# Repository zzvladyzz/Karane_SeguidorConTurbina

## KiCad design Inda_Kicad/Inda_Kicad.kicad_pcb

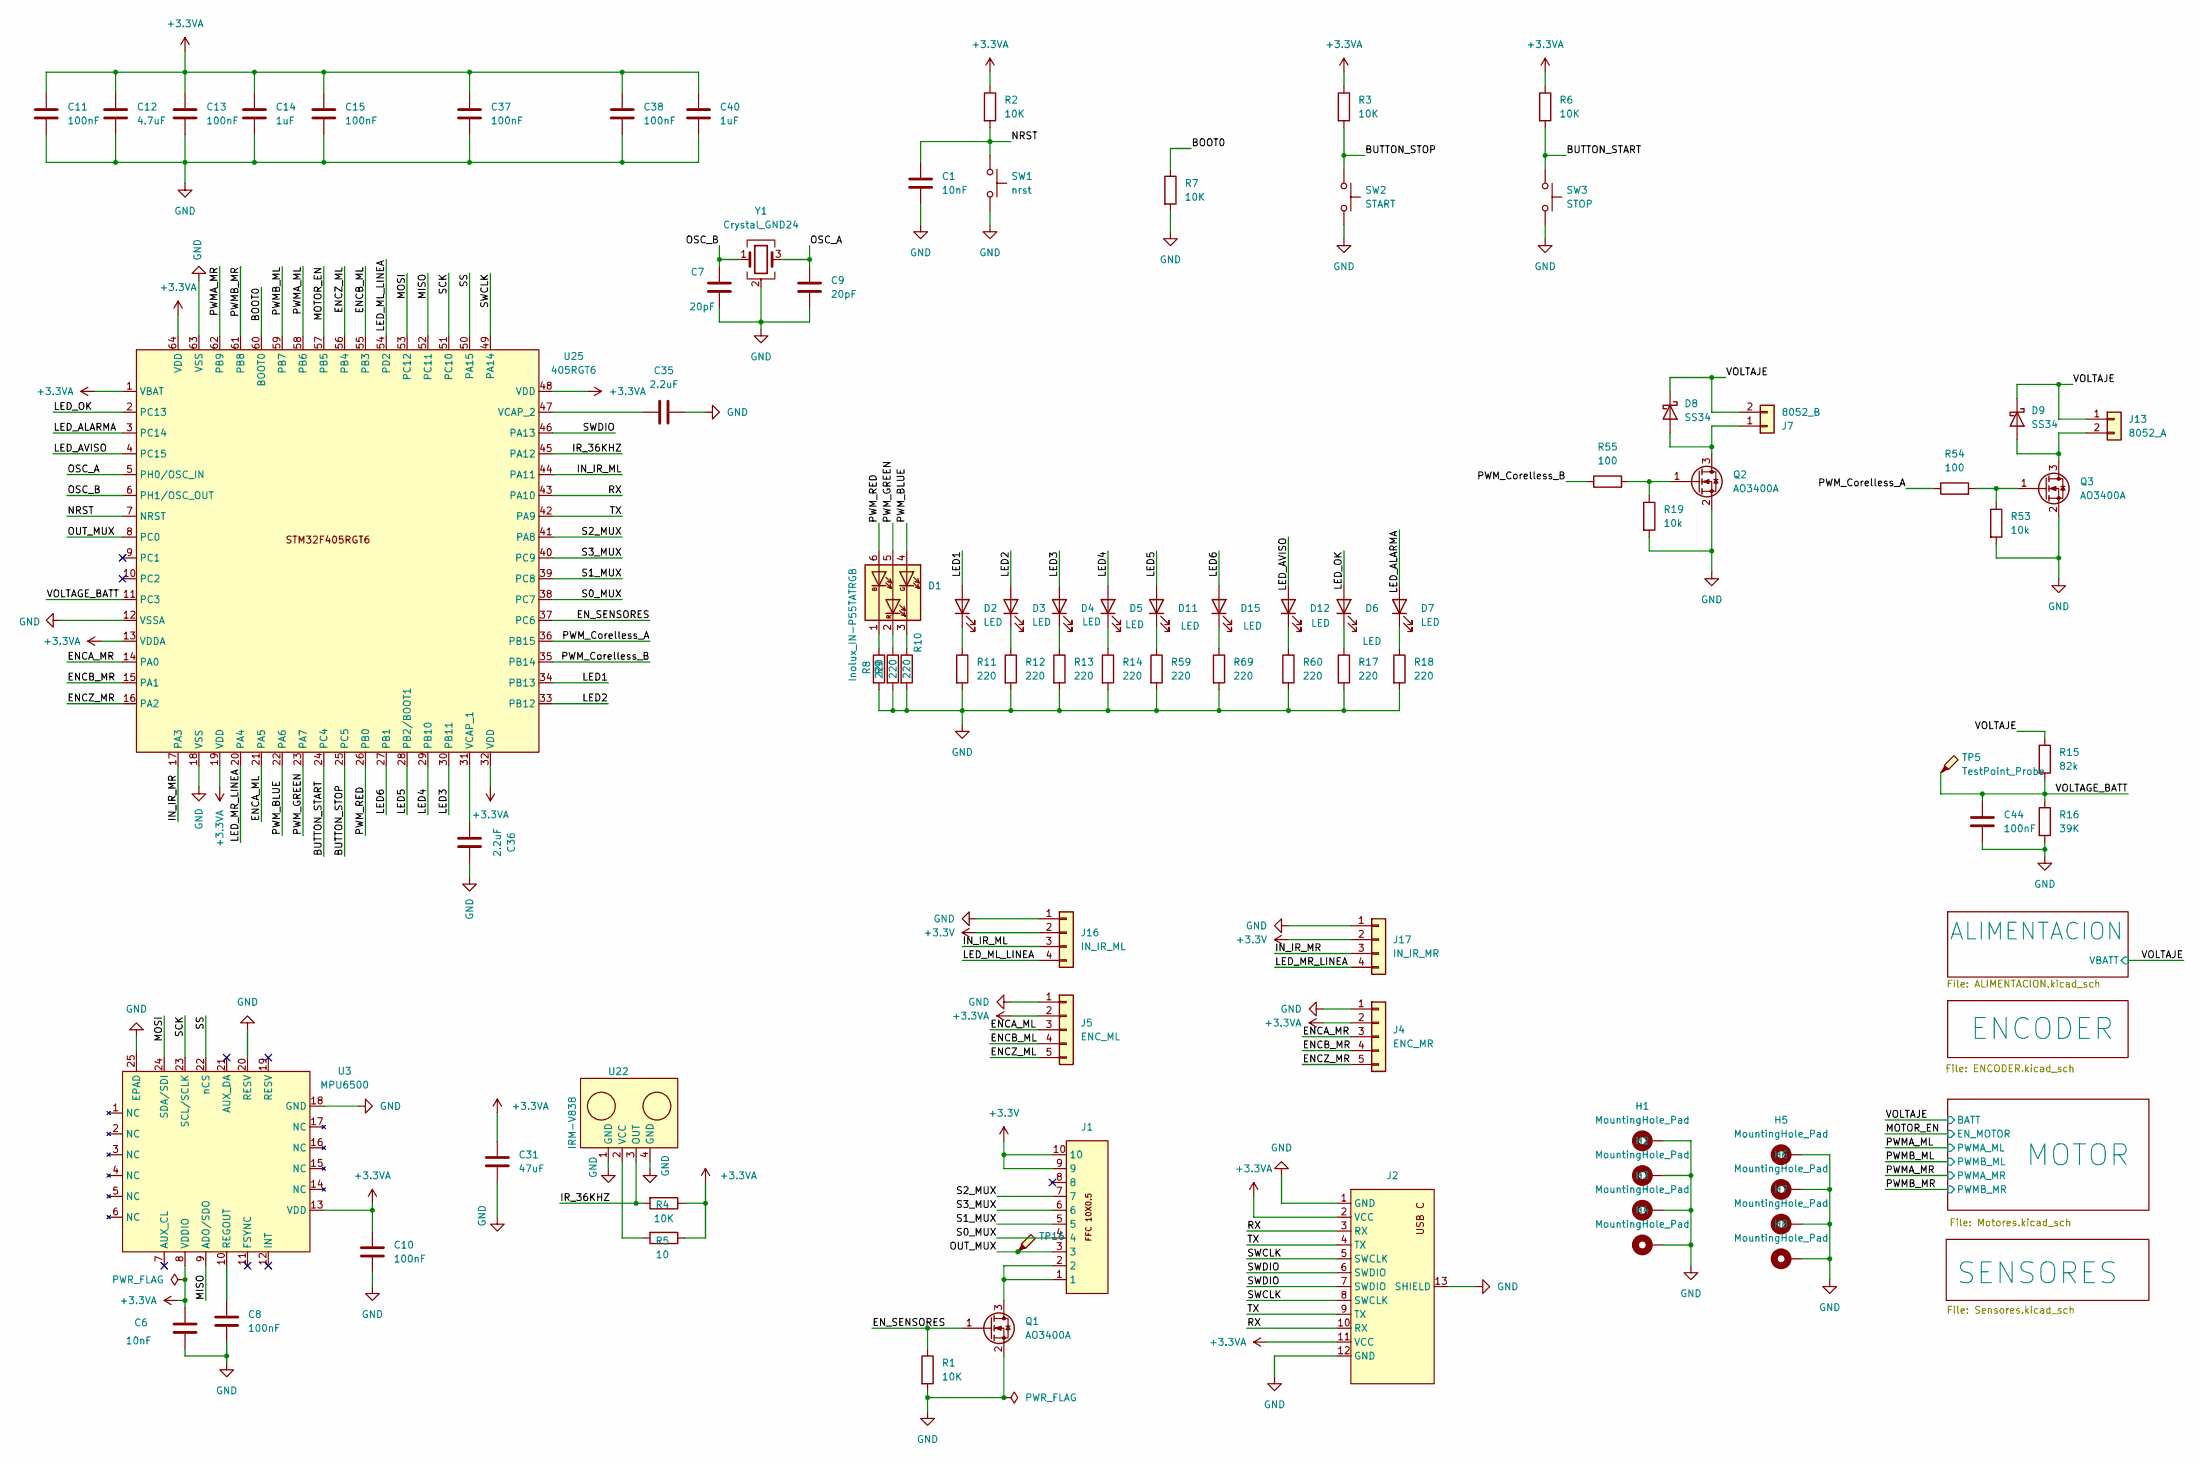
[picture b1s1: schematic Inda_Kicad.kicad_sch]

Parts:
C1, C6: 10nF; C_0603_1608Metric_Pad1.08x0.95mm_HandSolder
C7, C9: 20pF; C_0603_1608Metric_Pad1.08x0.95mm_HandSolder
C8, C10, C11, C13, C15, C37, C38, C44: 100nF; C_0603_1608Metric_Pad1.08x0.95mm_HandSolder
C12: 4.7uF; C_0603_1608Metric_Pad1.08x0.95mm_HandSolder
C14, C40: 1uF; C_0603_1608Metric_Pad1.08x0.95mm_HandSolder
C31: 47uF; C_0603_1608Metric_Pad1.08x0.95mm_HandSolder
C35, C36: 2.2uF; C_0603_1608Metric_Pad1.08x0.95mm_HandSolder
D1: Inolux_IN-P55TATRGB; LED_Inolux_IN-P55TATRGB_PLCC6_5.0x5.5mm_P1.8mm
D2, D3, D4, D5, D6, D7, D11, D12, D15: LED; LED_0805_2012Metric_Pad1.15x1.40mm_HandSolder
D8, D9: SS34; D_SMA
H1, H2, H3, H4, H5, H6, H7, H8: MountingHole_Pad; MountingHole_2.2mm_M2_ISO14580_Pad
J1: FFC_10x0.5
J2: usb_C_stm32
J4: ENC_MR; CONN_MT6701_THT_1.6mm_FEMALE
J5: ENC_ML; CONN_MT6701_THT_1.6mm_FEMALE
J7: 8052_B; JST_PH_B2B-PH-K_1x02_P2.00mm_Vertical
J13: 8052_A; JST_PH_B2B-PH-K_1x02_P2.00mm_Vertical
J16: IN_IR_ML; CONN_01X04_2IR_LINEA_FEMALE
J17: IN_IR_MR; CONN_01X04_2IR_LINEA_FEMALE
Q1, Q2, Q3: AO3400A; SOT-23
R1, R2, R3, R4, R6, R7: 10K; R_0603_1608Metric_Pad0.98x0.95mm_HandSolder
R5: 10; R_0603_1608Metric_Pad0.98x0.95mm_HandSolder
R8, R9, R10, R11, R12, R13, R14, R17, R18, R59, R60, R69: 220; R_0603_1608Metric_Pad0.98x0.95mm_HandSolder
R15: 82k; R_0603_1608Metric_Pad0.98x0.95mm_HandSolder
R16: 39K; R_0603_1608Metric_Pad0.98x0.95mm_HandSolder
R19, R53: 10k; R_0603_1608Metric_Pad0.98x0.95mm_HandSolder
R54, R55: 100; R_0603_1608Metric_Pad0.98x0.95mm_HandSolder
SW1: nrst; SW_Push_SPST_NO_Alps_SKRK
SW2: START; SW_Push_SPST_NO_Alps_SKRK
SW3: STOP; SW_Push_SPST_NO_Alps_SKRK
TP5, TP16: TestPoint_Probe; TestPoint_Pad_D1.0mm
U3: MPU6500; QFN-24-1EP_3x3mm_P0.4mm_EP1.75x1.6mm
U22: IRM-V838
U25: 405RGT6; LQFP-64_10x10mm_P0.5mm
Y1: Crystal_GND24; Crystal_SMD_3225-4Pin_3.2x2.5mm

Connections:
+3.3V: J1.9, J1.10, J16.2, J17.2; also elsewhere on the board
+3.3VA: C6.1, C10.1, C11.1, C12.1, C13.1, C14.1, C15.1, C31.1, C37.1, C38.1, C40.1, J2.2 (VCC), J2.11 (VCC), J4.2, J5.2, R2.1, R3.1, R4.1, R5.1, R6.1, U3.8 (VDDIO), U3.13 (VDD), U25.1 (VBAT), U25.13 (VDDA), U25.19 (VDD), U25.32 (VDD), U25.48 (VDD), U25.64 (VDD); also elsewhere on the board
/BOOT0: R7.1, U25.60 (BOOT0)
/BUTTON_START: R6.2, SW3.1, U25.24 (PC4)
/BUTTON_STOP: R3.2, SW2.1, U25.25 (PC5)
/ENCA_ML: J5.3, U25.21 (PA5)
/ENCA_MR: J4.3, U25.14 (PA0)
/ENCB_ML: J5.4, U25.55 (PB3)
/ENCB_MR: J4.4, U25.15 (PA1)
/ENCZ_ML: J5.5, U25.56 (PB4)
/ENCZ_MR: J4.5, U25.16 (PA2)
/EN_SENSORES: Q1.1 (G), R1.1, U25.37 (PC6)
/IN_IR_ML: J16.3, U25.44 (PA11)
/IN_IR_MR: J17.3, U25.17 (PA3)
/IR_36KHZ: R4.2, U22.3 (OUT), U25.45 (PA12)
/LED1: D2.2 (A), U25.34 (PB13)
/LED2: D3.2 (A), U25.33 (PB12)
/LED3: D4.2 (A), U25.30 (PB11)
/LED4: D5.2 (A), U25.29 (PB10)
/LED5: D11.2 (A), U25.28 (PB2/BOOT1)
/LED6: D15.2 (A), U25.27 (PB1)
/LED_ALARMA: D7.2 (A), U25.3 (PC14)
/LED_AVISO: D12.2 (A), U25.4 (PC15)
/LED_ML_LINEA: J16.4, U25.54 (PD2)
/LED_MR_LINEA: J17.4, U25.20 (PA4)
/LED_OK: D6.2 (A), U25.2 (PC13)
/MISO: U3.9 (ADO/SDO), U25.52 (PC11)
/MOSI: U3.24 (SDA/SDI), U25.53 (PC12)
/MOTOR_EN: U25.57 (PB5); also elsewhere on the board
/NRST: C1.1, R2.2, SW1.1, U25.7 (NRST)
/OSC_A: C9.1, U25.5 (PH0/OSC_IN), Y1.3
/OSC_B: C7.1, U25.6 (PH1/OSC_OUT), Y1.1
/OUT_MUX: J1.3, TP16.1 (1_1), U25.8 (PC0)
/PWMA_ML: U25.58 (PB6); also elsewhere on the board
/PWMA_MR: U25.62 (PB9); also elsewhere on the board
/PWMB_ML: U25.59 (PB7); also elsewhere on the board
/PWMB_MR: U25.61 (PB8); also elsewhere on the board
/PWM_BLUE: D1.4 (AG), U25.22 (PA6)
/PWM_Corelless_A: R54.1, U25.36 (PB15)
/PWM_Corelless_B: R55.1, U25.35 (PB14)
/PWM_GREEN: D1.5 (AR), U25.23 (PA7)
/PWM_RED: D1.6 (AB), U25.26 (PB0)
/RX: J2.3 (RX), J2.10 (RX), U25.43 (PA10)
/S0_MUX: J1.4, U25.38 (PC7)
/S1_MUX: J1.5, U25.39 (PC8)
/S2_MUX: J1.7, U25.41 (PA8)
/S3_MUX: J1.6, U25.40 (PC9)
/SCK: U3.23 (SCL/SCLK), U25.51 (PC10)
/SS: U3.22 (nCS), U25.50 (PA15)
/SWCLK: J2.5 (SWCLK), J2.8 (SWCLK), U25.49 (PA14)
/SWDIO: J2.6 (SWDIO), J2.7 (SWDIO), U25.46 (PA13)
/TX: J2.4 (TX), J2.9 (TX), U25.42 (PA9)
/VOLTAGE_BATT: C44.1, R15.2, R16.1, TP5.1 (1_1), U25.11 (PC3)
/VOLTAJE: D8.1 (K), D9.1 (K), J7.2, J13.1, R15.1; also elsewhere on the board
GND: C1.2, C6.2, C7.2, C8.2, C9.2, C10.2, C11.2, C12.2, C13.2, C14.2, C15.2, C31.2, C35.2, C36.2, C37.2, C38.2, C40.2, C44.2, H1.1 (1_1), H2.1 (1_1), H3.1 (1_1), H4.1 (1_1), H5.1 (1_1), H6.1 (1_1), H7.1 (1_1), H8.1 (1_1), J2.1 (GND), J2.12 (GND), J2.13 (SHIELD), J4.1, J5.1, J16.1, J17.1, Q1.2 (S), Q2.2 (S), Q3.2 (S), R1.2, R7.2, R8.2, R9.2, R10.2, R11.2, R12.2, R13.2, R14.2, R16.2, R17.2, R18.2, R19.2, R53.2, R59.2, R60.2, R69.2, SW1.2, SW2.2, SW3.2, U3.18 (GND), U3.20 (RESV), U3.25 (EPAD), U22.1 (GND), U22.4 (GND), U25.12 (VSSA), U25.18 (VSS), U25.63 (VSS), Y1.2 (G), Y1.4 (G); also elsewhere on the board
unnamed: D1.1 (KB), R8.1
unnamed: D1.3 (KG), R10.1
unnamed: D1.2 (KR), R9.1
unnamed: D2.1 (K), R11.1
unnamed: D3.1 (K), R12.1
unnamed: D4.1 (K), R13.1
unnamed: D5.1 (K), R14.1
unnamed: D6.1 (K), R17.1
unnamed: D7.1 (K), R18.1
unnamed: D8.2 (A), J7.1, Q2.3 (D)
unnamed: D9.2 (A), J13.2, Q3.3 (D)
unnamed: D11.1 (K), R59.1
unnamed: D12.1 (K), R60.1
unnamed: D15.1 (K), R69.1
unnamed: J1.1, J1.2, Q1.3 (D)
unnamed: Q2.1 (G), R19.1, R55.2
unnamed: Q3.1 (G), R53.1, R54.2
unnamed: C8.1, U3.10 (REGOUT)
unnamed: R5.2, U22.2 (VCC)
unnamed: C36.1, U25.31 (VCAP_1)
unnamed: C35.1, U25.47 (VCAP_2)

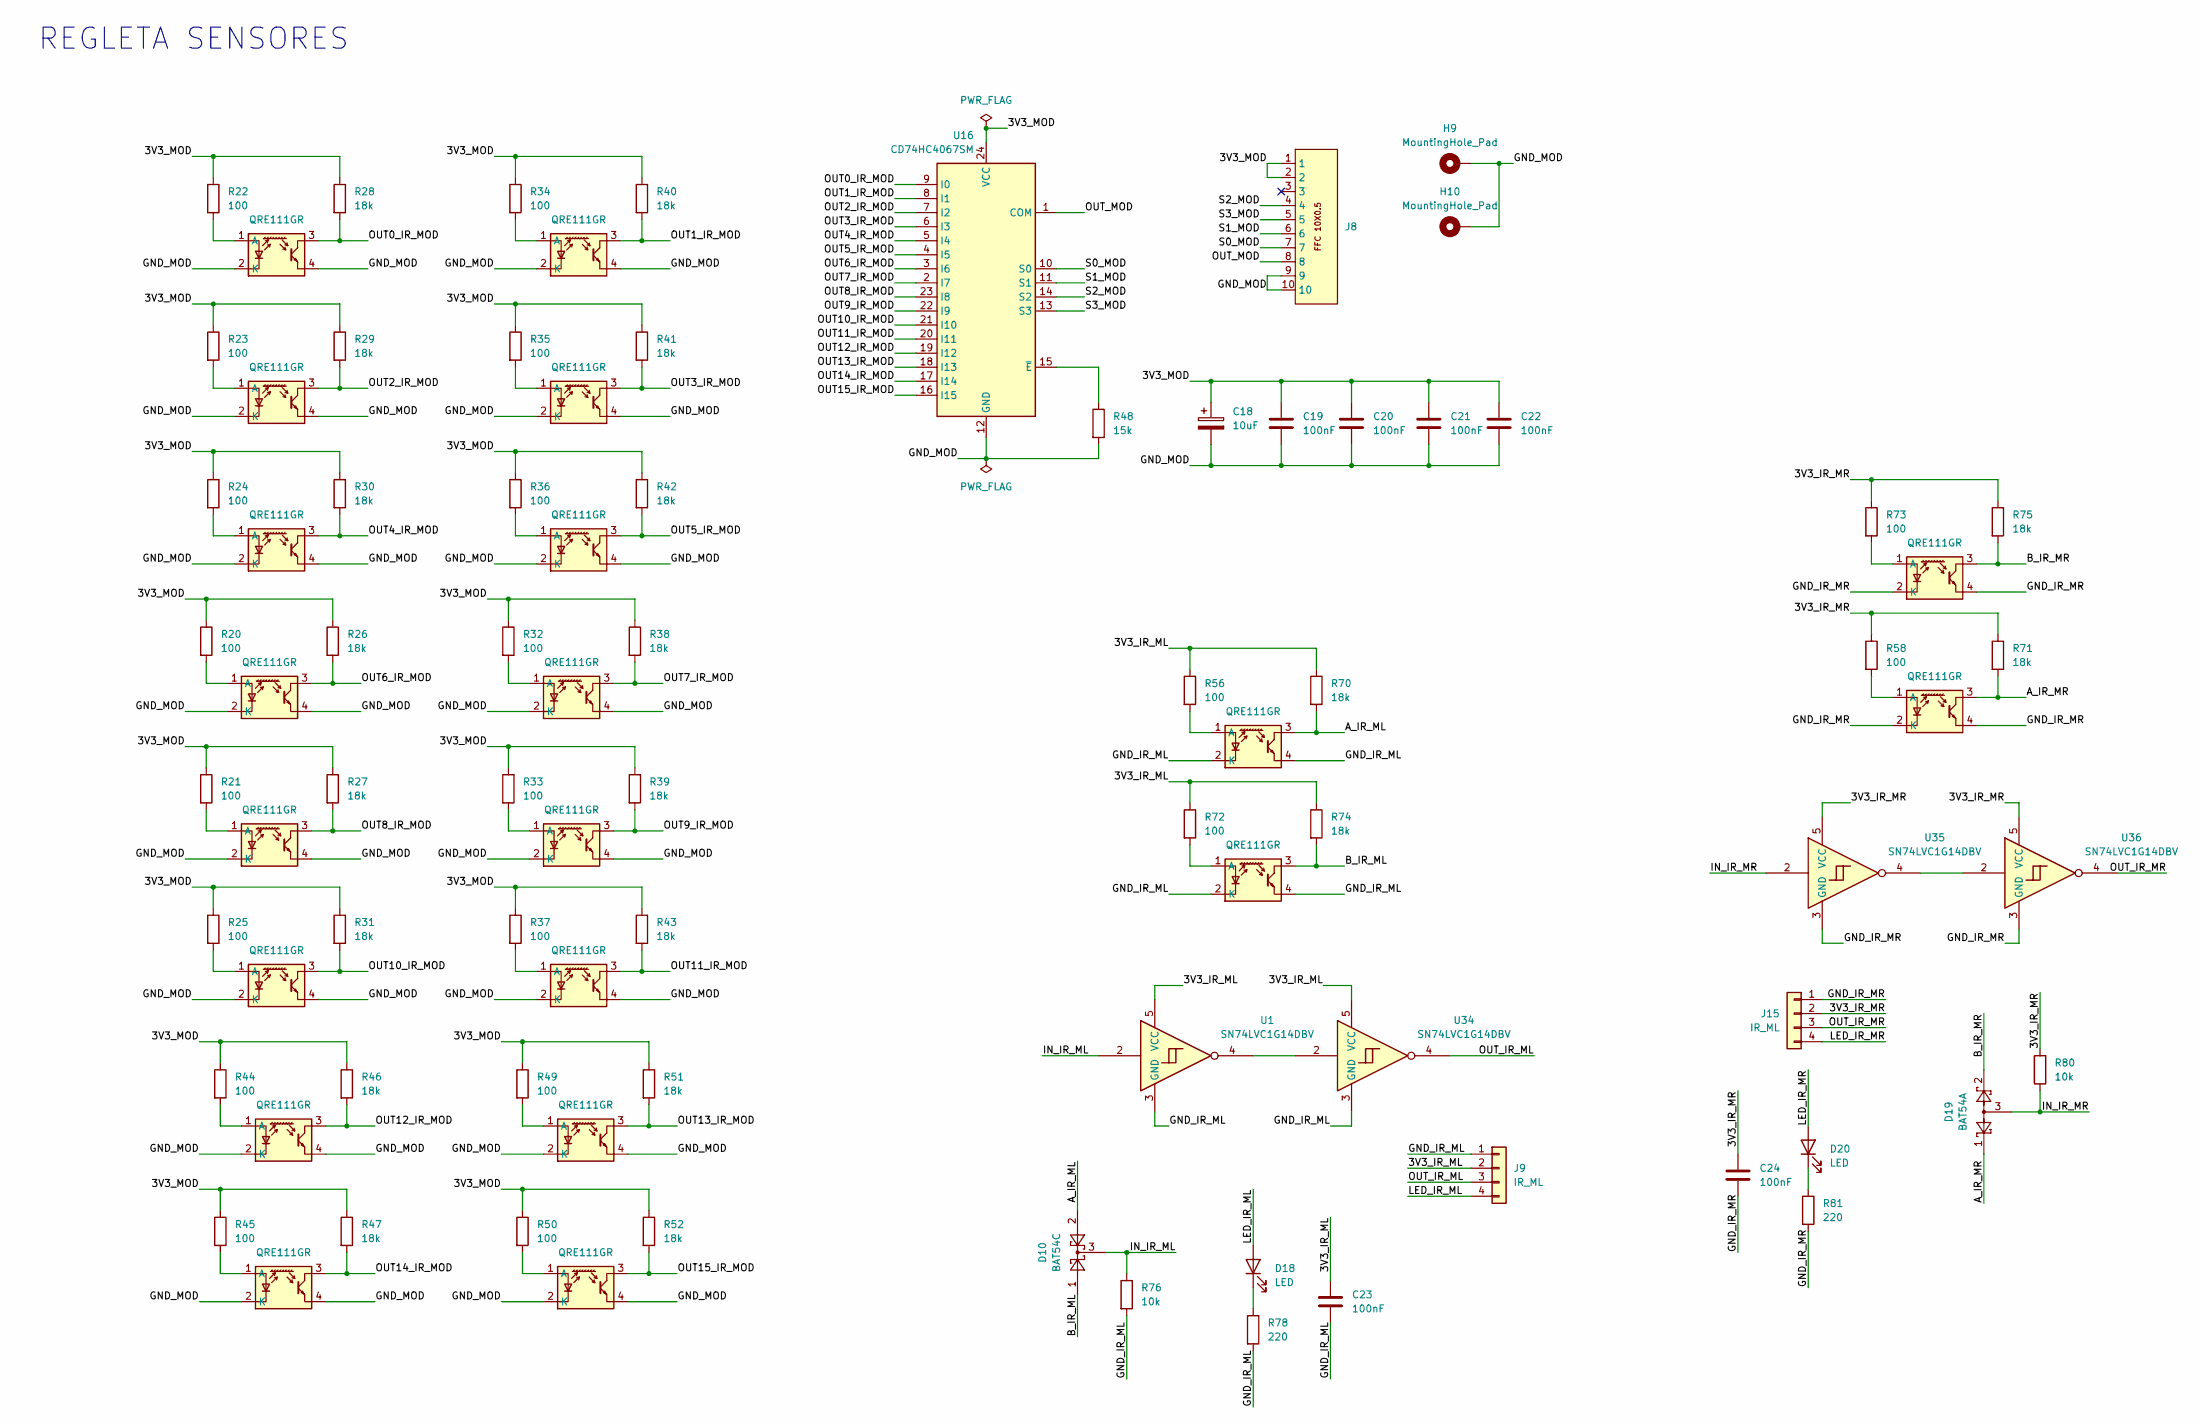
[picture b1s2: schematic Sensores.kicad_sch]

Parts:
C18: 10uF; CP_EIA-3216-12_Kemet-S
C19, C20, C21, C22, C23, C24: 100nF; C_0603_1608Metric_Pad1.08x0.95mm_HandSolder
D10: BAT54C; SOT-23
D18, D20: LED; LED_1206_3216Metric_Pad1.42x1.75mm_HandSolder
D19: BAT54A; SOT-23
H9, H10: MountingHole_Pad; MountingHole_2.2mm_M2_ISO14580_Pad
J8: FFC_10x0.5
J9, J15: IR_ML; CONN_01X04_2IR_LINEA_MALE
R20, R21, R22, R23, R24, R25, R32, R33, R34, R35, R36, R37, R44, R45, R49, R50, R56, R58, R72, R73: 100; R_0603_1608Metric_Pad0.98x0.95mm_HandSolder
R26, R27, R28, R29, R30, R31, R38, R39, R40, R41, R42, R43, R46, R47, R51, R52, R70, R71, R74, R75: 18k; R_0603_1608Metric_Pad0.98x0.95mm_HandSolder
R48: 15k; R_0603_1608Metric_Pad0.98x0.95mm_HandSolder
R76, R80: 10k; R_0603_1608Metric_Pad0.98x0.95mm_HandSolder
R78, R81: 220; R_0603_1608Metric_Pad0.98x0.95mm_HandSolder
U1, U34, U35, U36: SN74LVC1G14DBV; SOT-23-5
U4, U5, U6, U7, U8, U9, U10, U11, U12, U13, U14, U15, U17, U18, U19, U20, U30, U31, U32, U33: QRE111GR; QRE1113GR_IR
U16: CD74HC4067SM; SSOP-24_5.3x8.2mm_P0.65mm

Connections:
/SENSORES/3V3_IR_ML: C23.1, J9.2, R56.1, R70.1, R72.1, R74.1, U1.5 (VCC), U34.5 (VCC)
/SENSORES/3V3_IR_MR: C24.1, J15.2, R58.1, R71.1, R73.1, R75.1, R80.2, U35.5 (VCC), U36.5 (VCC)
/SENSORES/3V3_MOD: C18.1, C19.1, C20.1, C21.1, C22.1, J8.1, J8.2, R20.1, R21.1, R22.1, R23.1, R24.1, R25.1, R26.1, R27.1, R28.1, R29.1, R30.1, R31.1, R32.1, R33.1, R34.1, R35.1, R36.1, R37.1, R38.1, R39.1, R40.1, R41.1, R42.1, R43.1, R44.1, R45.1, R46.1, R47.1, R49.1, R50.1, R51.1, R52.1, U16.24 (VCC)
/SENSORES/A_IR_ML: D10.2, R70.2, U30.3
/SENSORES/A_IR_MR: D19.1, R71.2, U31.3
/SENSORES/B_IR_ML: D10.1, R74.2, U32.3
/SENSORES/B_IR_MR: D19.2, R75.2, U33.3
/SENSORES/GND_IR_ML: C23.2, J9.1, R76.2, R78.2, U1.3 (GND), U30.2 (K), U30.4, U32.2 (K), U32.4, U34.3 (GND)
/SENSORES/GND_IR_MR: C24.2, J15.1, R81.2, U31.2 (K), U31.4, U33.2 (K), U33.4, U35.3 (GND), U36.3 (GND)
/SENSORES/GND_MOD: C18.2, C19.2, C20.2, C21.2, C22.2, H9.1 (1_1), H10.1 (1_1), J8.9, J8.10, R48.2, U4.2 (K), U4.4, U5.2 (K), U5.4, U6.2 (K), U6.4, U7.2 (K), U7.4, U8.2 (K), U8.4, U9.2 (K), U9.4, U10.2 (K), U10.4, U11.2 (K), U11.4, U12.2 (K), U12.4, U13.2 (K), U13.4, U14.2 (K), U14.4, U15.2 (K), U15.4, U16.12 (GND), U17.2 (K), U17.4, U18.2 (K), U18.4, U19.2 (K), U19.4, U20.2 (K), U20.4
/SENSORES/IN_IR_ML: D10.3, R76.1, U1.2
/SENSORES/IN_IR_MR: D19.3, R80.1, U35.2
/SENSORES/LED_IR_ML: D18.2 (A), J9.4
/SENSORES/LED_IR_MR: D20.2 (A), J15.4
/SENSORES/OUT0_IR_MOD: R28.2, U6.3, U16.9 (I0)
/SENSORES/OUT1_IR_MOD: R40.2, U12.3, U16.8 (I1)
/SENSORES/OUT2_IR_MOD: R29.2, U7.3, U16.7 (I2)
/SENSORES/OUT3_IR_MOD: R41.2, U13.3, U16.6 (I3)
/SENSORES/OUT4_IR_MOD: R30.2, U8.3, U16.5 (I4)
/SENSORES/OUT5_IR_MOD: R42.2, U14.3, U16.4 (I5)
/SENSORES/OUT6_IR_MOD: R26.2, U4.3, U16.3 (I6)
/SENSORES/OUT7_IR_MOD: R38.2, U10.3, U16.2 (I7)
/SENSORES/OUT8_IR_MOD: R27.2, U5.3, U16.23 (I8)
/SENSORES/OUT9_IR_MOD: R39.2, U11.3, U16.22 (I9)
/SENSORES/OUT10_IR_MOD: R31.2, U9.3, U16.21 (I10)
/SENSORES/OUT11_IR_MOD: R43.2, U15.3, U16.20 (I11)
/SENSORES/OUT12_IR_MOD: R46.2, U16.19 (I12), U17.3
/SENSORES/OUT13_IR_MOD: R51.2, U16.18 (I13), U19.3
/SENSORES/OUT14_IR_MOD: R47.2, U16.17 (I14), U18.3
/SENSORES/OUT15_IR_MOD: R52.2, U16.16 (I15), U20.3
/SENSORES/OUT_IR_ML: J9.3, U34.4
/SENSORES/OUT_IR_MR: J15.3, U36.4
/SENSORES/OUT_MOD: J8.8, U16.1 (COM)
/SENSORES/S0_MOD: J8.7, U16.10 (S0)
/SENSORES/S1_MOD: J8.6, U16.11 (S1)
/SENSORES/S2_MOD: J8.4, U16.14 (S2)
/SENSORES/S3_MOD: J8.5, U16.13 (S3)
unnamed: D18.1 (K), R78.1
unnamed: D20.1 (K), R81.1
unnamed: U1.4, U34.2
unnamed: R20.2, U4.1 (A)
unnamed: R21.2, U5.1 (A)
unnamed: R22.2, U6.1 (A)
unnamed: R23.2, U7.1 (A)
unnamed: R24.2, U8.1 (A)
unnamed: R25.2, U9.1 (A)
unnamed: R32.2, U10.1 (A)
unnamed: R33.2, U11.1 (A)
unnamed: R34.2, U12.1 (A)
unnamed: R35.2, U13.1 (A)
unnamed: R36.2, U14.1 (A)
unnamed: R37.2, U15.1 (A)
unnamed: R48.1, U16.15 (~E)
unnamed: R44.2, U17.1 (A)
unnamed: R45.2, U18.1 (A)
unnamed: R49.2, U19.1 (A)
unnamed: R50.2, U20.1 (A)
unnamed: R56.2, U30.1 (A)
unnamed: R58.2, U31.1 (A)
unnamed: R72.2, U32.1 (A)
unnamed: R73.2, U33.1 (A)
unnamed: U35.4, U36.2

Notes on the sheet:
REGLETA SENSORES

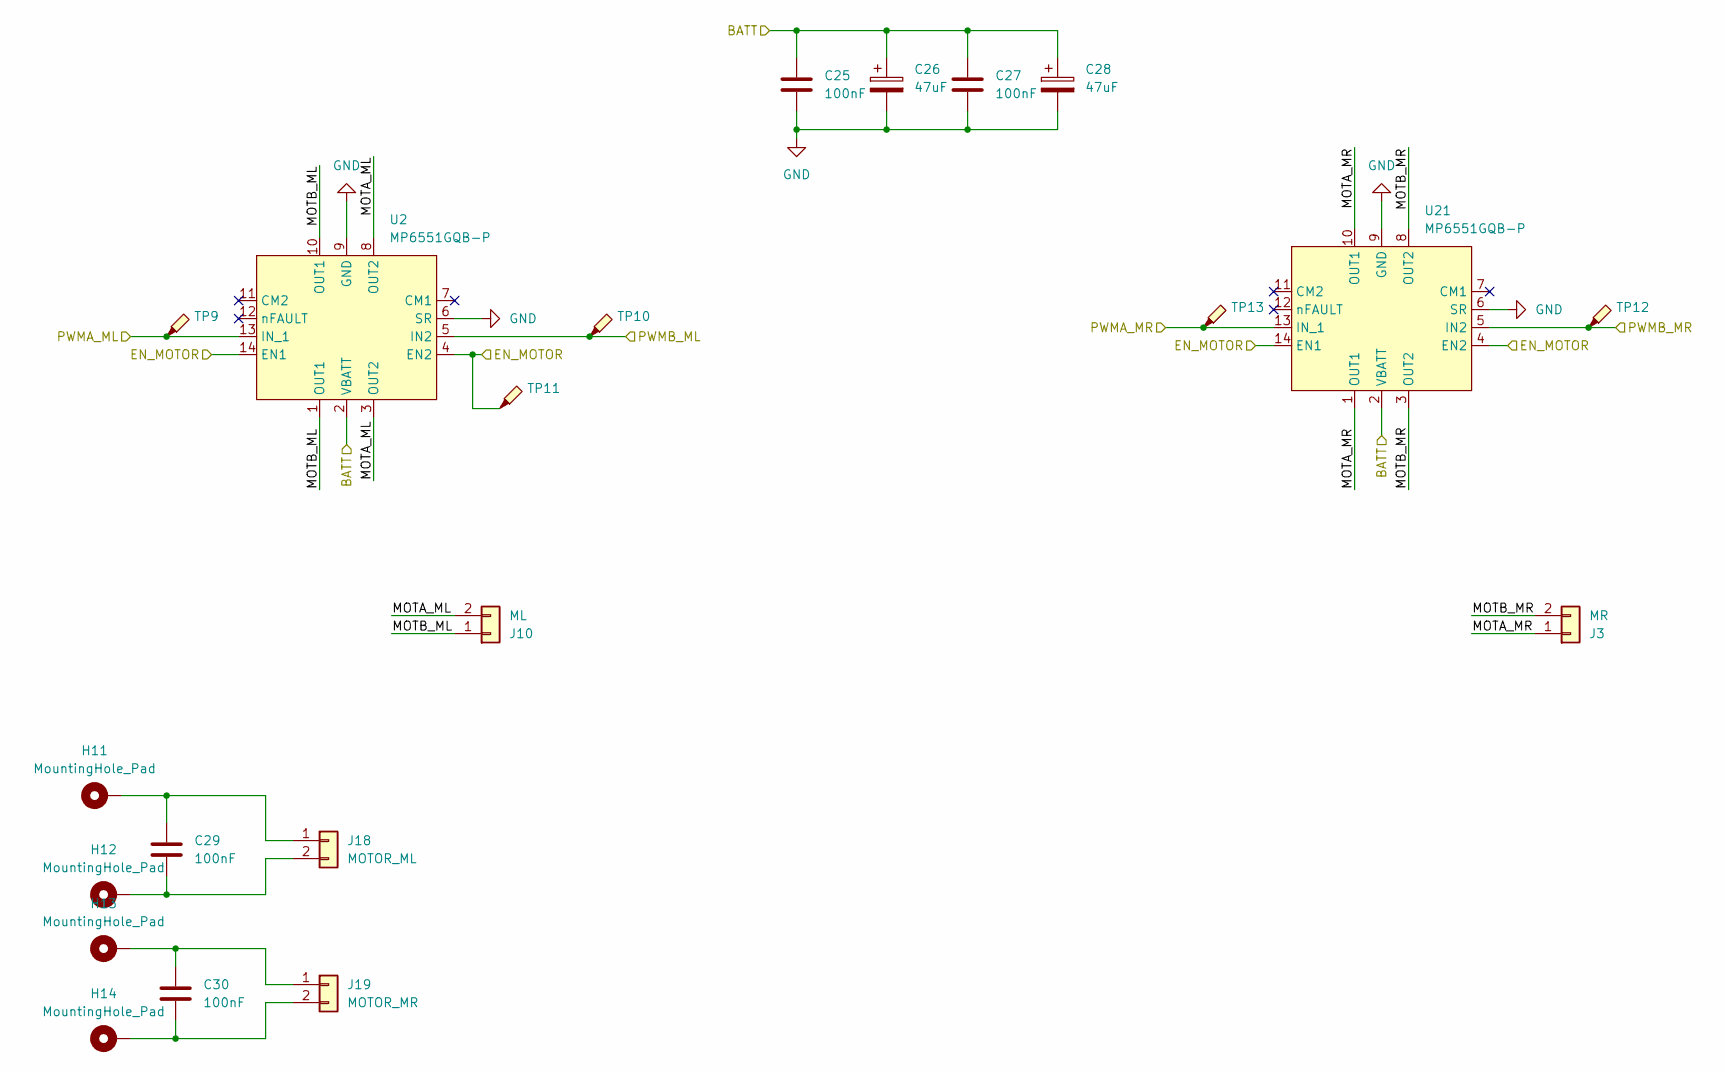
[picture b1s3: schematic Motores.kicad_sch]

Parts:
C25, C27: 100nF; C_0603_1608Metric_Pad1.08x0.95mm_HandSolder
C26, C28: 47uF; CP_EIA-7343-15_Kemet-W_HandSolder
C29, C30: 100nF; C_0805_2012Metric_Pad1.18x1.45mm_HandSolder
H11, H12, H13, H14: MountingHole_Pad; PAD_MOTOR_1725
J3: MR; JST_PH_B2B-PH-K_1x02_P2.00mm_Vertical
J10: ML; JST_PH_B2B-PH-K_1x02_P2.00mm_Vertical
J18: MOTOR_ML; JST_PH_S2B-PH-K_1x02_P2.00mm_Horizontal
J19: MOTOR_MR; JST_PH_S2B-PH-K_1x02_P2.00mm_Horizontal
TP9, TP10, TP11, TP12, TP13: TestPoint_Probe; TestPoint_Pad_D1.0mm
U2, U21: MP6551GQB-P; MP6551

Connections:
/MOTOR/MOTA_ML: J10.2, U2.3 (OUT2), U2.8 (OUT2)
/MOTOR/MOTA_MR: J3.1, U21.1 (OUT1), U21.10 (OUT1)
/MOTOR/MOTB_ML: J10.1, U2.1 (OUT1), U2.10 (OUT1)
/MOTOR/MOTB_MR: J3.2, U21.3 (OUT2), U21.8 (OUT2)
/MOTOR_EN: TP11.1 (1_1), U2.4 (EN2), U2.14 (EN1), U21.4 (EN2), U21.14 (EN1); also elsewhere on the board
/PWMA_ML: TP9.1 (1_1), U2.13 (IN_1); also elsewhere on the board
/PWMA_MR: TP13.1 (1_1), U21.13 (IN_1); also elsewhere on the board
/PWMB_ML: TP10.1 (1_1), U2.5 (IN2); also elsewhere on the board
/PWMB_MR: TP12.1 (1_1), U21.5 (IN2); also elsewhere on the board
/VOLTAJE: C25.1, C26.1, C27.1, C28.1, U2.2 (VBATT), U21.2 (VBATT); also elsewhere on the board
GND: C25.2, C26.2, C27.2, C28.2, U2.6 (SR), U2.9 (GND), U21.6 (SR), U21.9 (GND); also elsewhere on the board
unnamed: C29.1, H11.1 (1_1), J18.1
unnamed: C29.2, H12.1 (1_1), J18.2
unnamed: C30.1, H13.1 (1_1), J19.1
unnamed: C30.2, H14.1 (1_1), J19.2

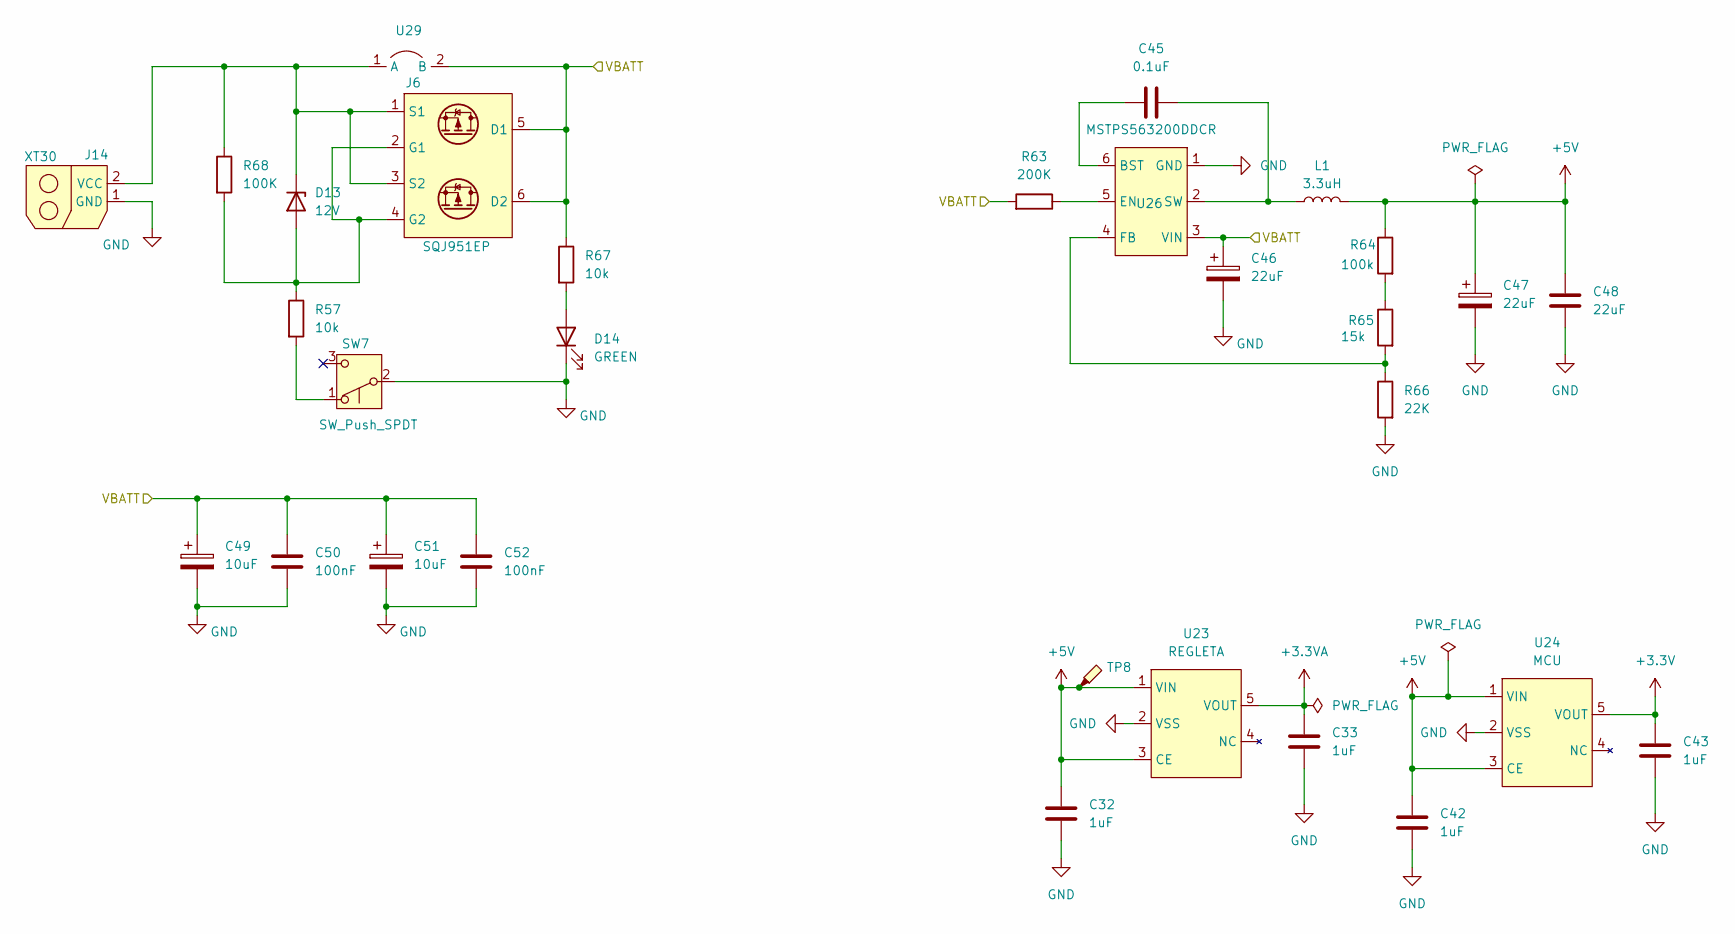
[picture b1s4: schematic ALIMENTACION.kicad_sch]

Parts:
C32, C33, C42, C43: 1uF; C_0603_1608Metric_Pad1.08x0.95mm_HandSolder
C45: 0.1uF; C_0603_1608Metric
C46, C47: 22uF; CP_EIA-3528-15_AVX-H_HandSolder
C48: 22uF; C_0603_1608Metric
C49, C51: 10uF; CP_EIA-3528-15_AVX-H_HandSolder
C50, C52: 100nF; C_0603_1608Metric
D13: 12V; R_1206_3216Metric_Pad1.30x1.75mm_HandSolder
D14: GREEN; LED_1206_3216Metric_Pad1.42x1.75mm_HandSolder
J6: SQJ951EP; PowerPAK_SO-8_Dual
J14: XT30; XT30U-F_1x02_P5.0mm_Vertical
L1: 3.3uH; L_Sunlord_MWSA0402S
R57, R67: 10k; R_0603_1608Metric_Pad0.98x0.95mm_HandSolder
R63: 200K; R_0603_1608Metric_Pad0.98x0.95mm_HandSolder
R64: 100k; R_0603_1608Metric_Pad0.98x0.95mm_HandSolder
R65: 15k; R_0603_1608Metric_Pad0.98x0.95mm_HandSolder
R66: 22K; R_0603_1608Metric_Pad0.98x0.95mm_HandSolder
R68: 100K; R_0603_1608Metric_Pad0.98x0.95mm_HandSolder
SW7: SW_Push_SPDT; SW_SPDT_PCM12
TP8: TestPoint_Probe; TestPoint_Pad_D1.0mm
U23: REGLETA; SOT-23-5_HandSoldering
U24: MCU; SOT-23-5_HandSoldering
U26: MSTPS563200DDCR; SOT-23-6
U29: BRIDGE_2P

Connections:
+3.3V: C43.1, U24.5 (VOUT); also elsewhere on the board
+3.3VA: C33.1, U23.5 (VOUT); also elsewhere on the board
+5V: C32.1, C42.1, C47.1, C48.2, L1.1, R64.1, TP8.1 (1_1), U23.1 (VIN), U23.3 (CE), U24.1 (VIN), U24.3 (CE)
/VOLTAJE: C46.1, C49.1, C50.2, C51.1, C52.2, J6.5 (D1), J6.6 (D2), R63.2, R67.1, U26.3 (VIN), U29.2 (B); also elsewhere on the board
GND: C32.2, C33.2, C42.2, C43.2, C46.2, C47.2, C48.1, C49.2, C50.1, C51.2, C52.1, D14.1 (K), J14.1 (GND), R66.2, SW7.2 (B), U23.2 (VSS), U24.2 (VSS), U26.1 (GND); also elsewhere on the board
unnamed: D13.2 (A), J6.2 (G1), J6.4 (G2), R57.1, R68.2
unnamed: D13.1 (K), J6.1 (S1), J6.3 (S2), J14.2 (VCC), R68.1, U29.1 (A)
unnamed: D14.2 (A), R67.2
unnamed: R64.2, R65.1
unnamed: R57.2, SW7.1 (A)
unnamed: C45.1, U26.6 (BST)
unnamed: R63.1, U26.5 (EN)
unnamed: R65.2, R66.1, U26.4 (FB)
unnamed: C45.2, L1.2, U26.2 (SW)

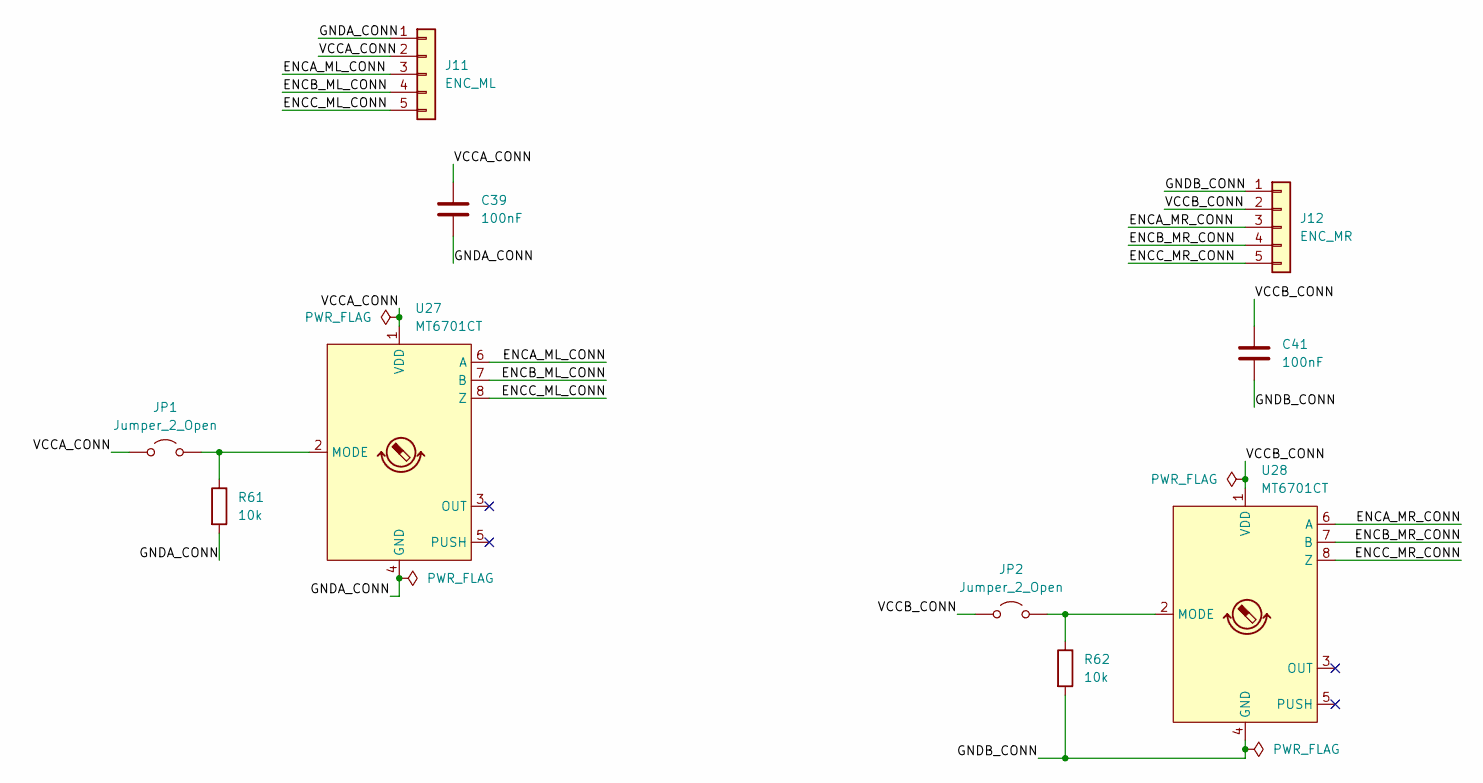
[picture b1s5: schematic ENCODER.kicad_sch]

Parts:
C39, C41: 100nF; C_0603_1608Metric_Pad1.08x0.95mm_HandSolder
J11: ENC_ML; CONN_MT6701_THT_1.6mm_MALE
J12: ENC_MR; CONN_MT6701_THT_1.6mm_MALE
JP1, JP2: Jumper_2_Open; SolderJumper-2_P1.3mm_Open_RoundedPad1.0x1.5mm
R61, R62: 10k; R_0603_1608Metric_Pad0.98x0.95mm_HandSolder
U27, U28: MT6701CT; SO-8_3.9x4.9mm_P1.27mm

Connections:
/ENCODER/ENCA_ML_CONN: J11.3, U27.6 (A)
/ENCODER/ENCA_MR_CONN: J12.3, U28.6 (A)
/ENCODER/ENCB_ML_CONN: J11.4, U27.7 (B)
/ENCODER/ENCB_MR_CONN: J12.4, U28.7 (B)
/ENCODER/ENCC_ML_CONN: J11.5, U27.8 (Z)
/ENCODER/ENCC_MR_CONN: J12.5, U28.8 (Z)
/ENCODER/GNDA_CONN: C39.2, J11.1, R61.2, U27.4 (GND)
/ENCODER/GNDB_CONN: C41.2, J12.1, R62.2, U28.4 (GND)
/ENCODER/VCCA_CONN: C39.1, J11.2, JP1.1 (A), U27.1 (VDD)
/ENCODER/VCCB_CONN: C41.1, J12.2, JP2.1 (A), U28.1 (VDD)
unnamed: JP1.2 (B), R61.1, U27.2 (MODE)
unnamed: JP2.2 (B), R62.1, U28.2 (MODE)

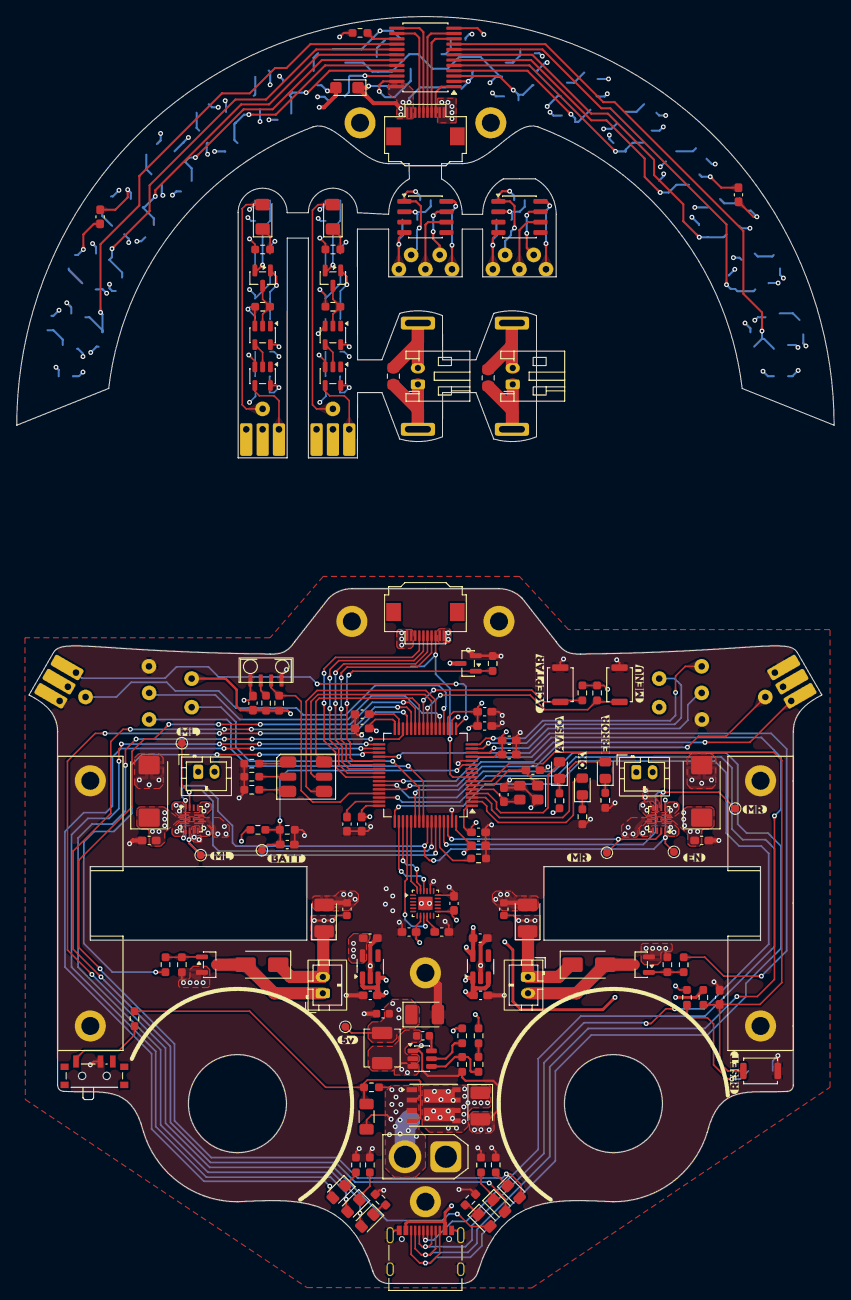
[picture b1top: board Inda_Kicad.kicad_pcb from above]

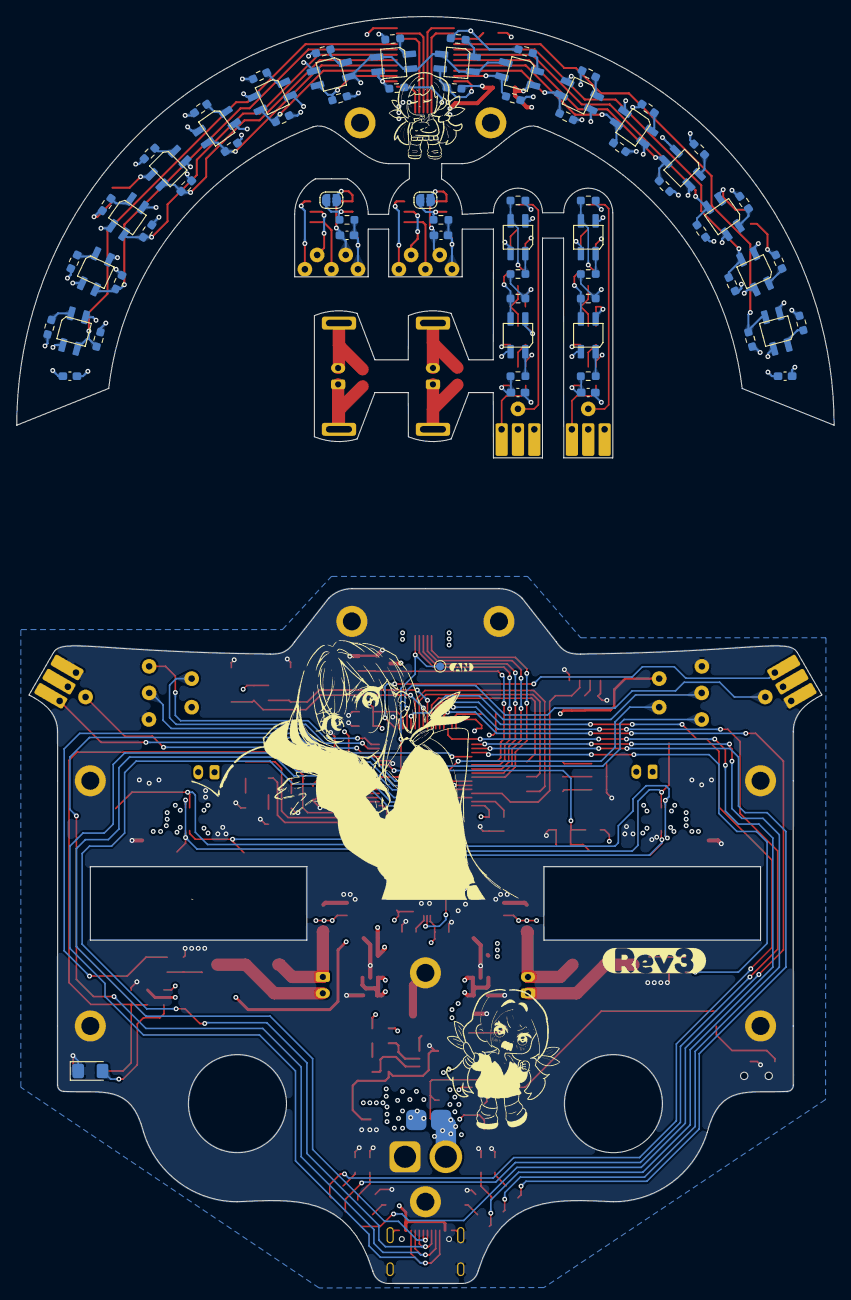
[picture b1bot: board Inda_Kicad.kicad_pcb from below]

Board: 4 copper layers, 100.0 x 155.0 mm, 245 parts (75 on the bottom side), 168 nets.

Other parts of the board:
kibuzzard-6A90F0A5: G***; kibuzzard-6A90F0A5
kibuzzard-6A90F0BB: G***; kibuzzard-6A90F0BB
kibuzzard-6A90F0C9: G***; kibuzzard-6A90F0C9
kibuzzard-6A90F0F9: G***; kibuzzard-6A90F0F9
kibuzzard-6A90F119: G***; kibuzzard-6A90F119
kibuzzard-6A90F136: G***; kibuzzard-6A90F136
kibuzzard-6A97CCFF: G***; kibuzzard-6A97CCFF
kibuzzard-6A9254A2: G***; kibuzzard-6A9254A2
kibuzzard-6A9254AE: G***; kibuzzard-6A9254AE
kibuzzard-6A9254B8, kibuzzard-6A9254B8#2: G***; kibuzzard-6A9254B8
kibuzzard-6A9255C9: G***; kibuzzard-6A9255C9
kibuzzard-6A925322: G***; kibuzzard-6A925322
kibuzzard-6A925429: G***; kibuzzard-6A925429
kibuzzard-6A925561: G***; kibuzzard-6A925561
